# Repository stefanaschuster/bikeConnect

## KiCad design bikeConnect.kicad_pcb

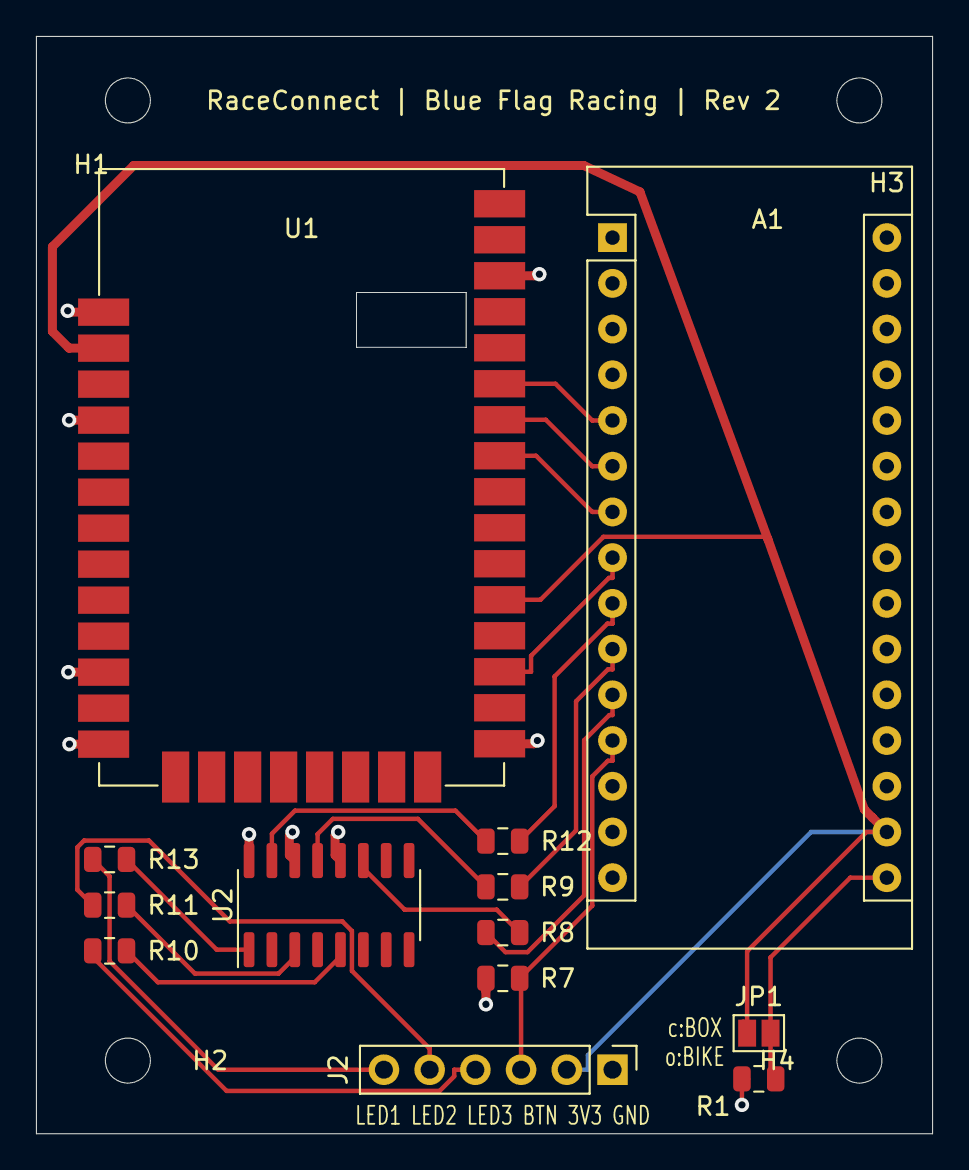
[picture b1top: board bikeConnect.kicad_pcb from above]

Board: 2 copper layers, 49.8 x 61.0 mm, 17 parts (0 on the bottom side), 20 nets.

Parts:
A1: Arduino_Nano_v3.x; Arduino_Nano
H1, H2, H3, H4: MountingHole; MountingHole_2.5mm
J2: Conn_01x06_Female; PinHeader_1x06_P2.54mm_Vertical
JP1: SolderJumper_2_Open; SolderJumper-2_P1.3mm_Open_Pad1.0x1.5mm
R1, R7, R8, R9, R12: 1k; R_0805_2012Metric
R10, R11, R13: 60; R_0805_2012Metric
U1: XBee_SMT; Digi_XBee_SMT
U2: MMPQ3904; SOIC-16_3.9x9.9mm_P1.27mm

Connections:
+3V3: A1.17, J2.2, JP1.2, U1.2, U1.26
GND: A1.4, A1.29, J2.1, R1.1, R7.1, U1.1, U1.4, U1.11, U1.13, U1.22, U1.35, U2.12, U2.14, U2.16
unnamed: A1.5, U1.32
unnamed: A1.6, U1.31
unnamed: A1.7, U1.30
unnamed: A1.8, U1.24
unnamed: A1.9, R12.2
unnamed: A1.10, R9.2
unnamed: A1.11, R8.2
unnamed: A1.12, J2.3, R7.2
unnamed: A1.16, JP1.1, R1.2
unnamed: J2.4, R10.1
unnamed: J2.5, R11.1
unnamed: J2.6, R13.1
unnamed: R8.1, U2.11
unnamed: R9.1, U2.13
unnamed: R10.2, U2.5
unnamed: R11.2, U2.3
unnamed: R12.1, U2.15
unnamed: R13.2, U2.1
